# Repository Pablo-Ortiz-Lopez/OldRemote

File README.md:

## OldRemote

This repository consists of the reverse engineering of a garage remote design by spanish company JCM dated around 1995. It emits an ASK signal, which encodes the value of a physical trinary selector, using a 280MHz carrier wave.

### Contents
This repository contains the following files
* Schematic of the design (KiCad)
* Approximate PCB Layout of the design (KiCad)
* Datasheets of various components used

For more information, don't hesitate to check out my blog: [ortizma.com](https://ortizma.com), or contact me via [pabloortiz132@gmail.com](mailto:pabloortiz132@gmail.com)

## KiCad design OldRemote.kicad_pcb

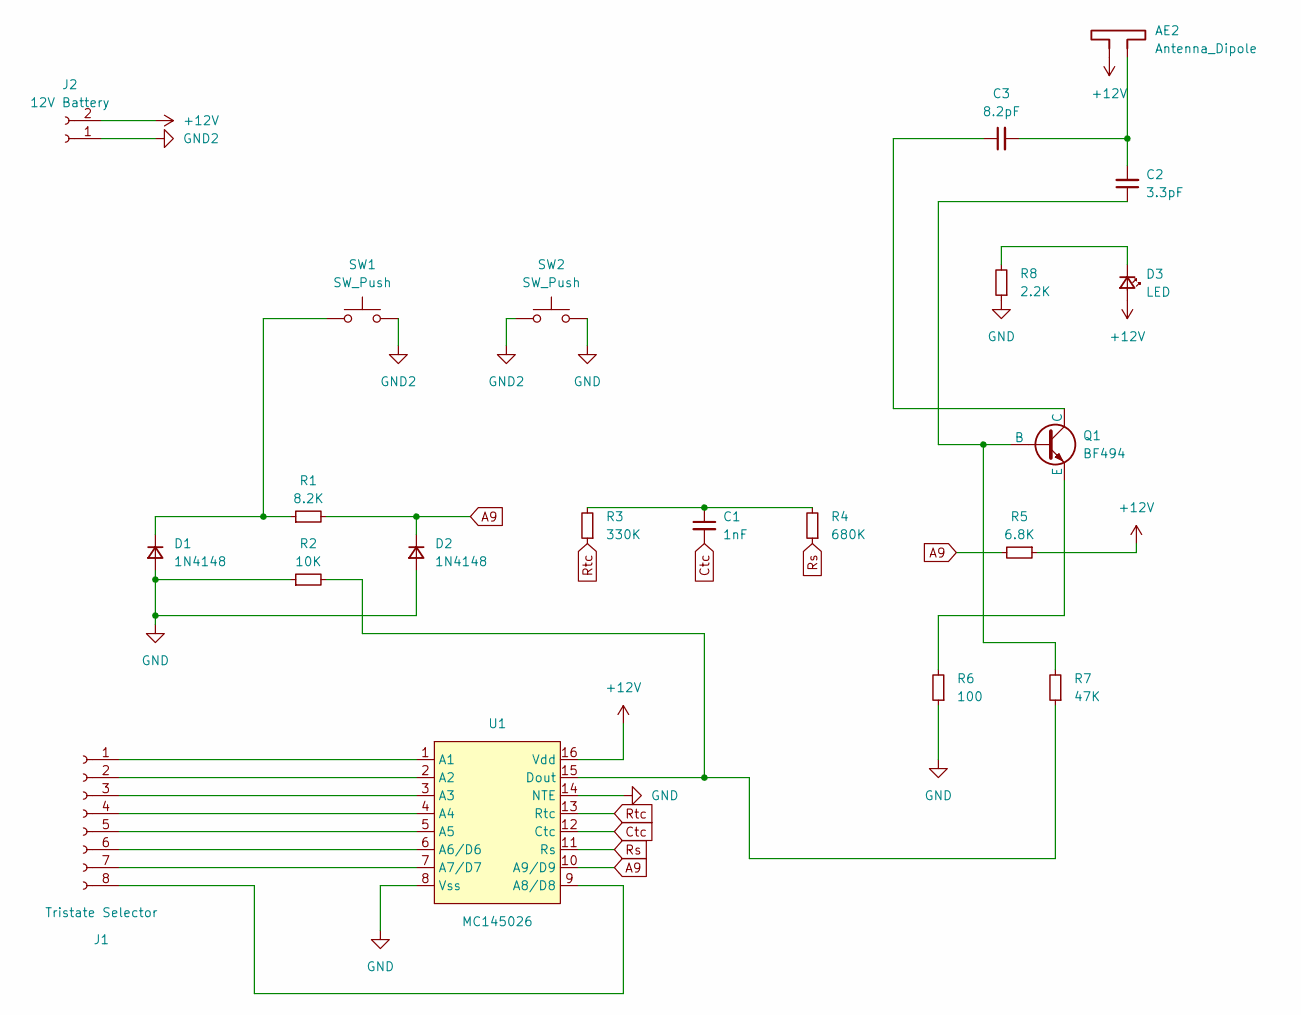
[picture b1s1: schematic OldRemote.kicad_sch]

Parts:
AE2: Antenna_Dipole; PinSocket_1x02_P2.54mm_Vertical
C1: 1nF; C_Rect_L4.0mm_W2.5mm_P2.50mm
C2: 3.3pF; C_Disc_D3.0mm_W1.6mm_P2.50mm
C3: 8.2pF; C_Disc_D3.0mm_W1.6mm_P2.50mm
D1, D2: 1N4148; D_DO-35_SOD27_P7.62mm_Horizontal
D3: LED; LED_D3.0mm_FlatTop
J1: Tristate Selector; PinSocket_1x08_P2.54mm_Horizontal
J2: 12V Battery; PinSocket_1x02_P2.54mm_Vertical
Q1: BF494; TO-92
R1: 8.2K; R_Axial_DIN0204_L3.6mm_D1.6mm_P5.08mm_Horizontal
R2: 10K; R_Axial_DIN0204_L3.6mm_D1.6mm_P5.08mm_Horizontal
R3: 330K; R_Axial_DIN0204_L3.6mm_D1.6mm_P5.08mm_Horizontal
R4: 680K; R_Axial_DIN0204_L3.6mm_D1.6mm_P5.08mm_Horizontal
R5: 6.8K; R_Axial_DIN0204_L3.6mm_D1.6mm_P5.08mm_Horizontal
R6: 100; R_Axial_DIN0204_L3.6mm_D1.6mm_P5.08mm_Horizontal
R7: 47K; R_Axial_DIN0204_L3.6mm_D1.6mm_P5.08mm_Horizontal
R8: 2.2K; R_Axial_DIN0204_L3.6mm_D1.6mm_P5.08mm_Horizontal
SW1, SW2: SW_Push; 4.5mm switch
U1: MC145026; DIP-16_W7.62mm

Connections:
+12V: AE2.1, D3.2 (A), J2.2, R5.1, U1.16 (Vdd)
A9: D2.1 (K), R1.2, R5.2, U1.10 (A9/D9)
Ctc: C1.2, U1.12 (Ctc)
GND: D1.2 (A), D2.2 (A), R2.1, R6.1, R8.1, SW2.2, U1.8 (Vss), U1.14 (NTE)
GND2: J2.1, SW1.2, SW2.1
unnamed: AE2.2, C2.2, C3.2
unnamed: C1.1, R3.2, R4.2
unnamed: D1.1 (K), R1.1, SW1.1
unnamed: D3.1 (K), R8.2
unnamed: J1.1, U1.1 (A1)
unnamed: J1.2, U1.2 (A2)
unnamed: J1.3, U1.3 (A3)
unnamed: J1.4, U1.4 (A4)
unnamed: J1.5, U1.5 (A5)
unnamed: J1.6, U1.6 (A6/D6)
unnamed: J1.7, U1.7 (A7/D7)
unnamed: J1.8, U1.9 (A8/D8)
unnamed: C2.1, Q1.2 (B), R7.2
unnamed: C3.1, Q1.1 (C)
unnamed: Q1.3 (E), R6.2
unnamed: R2.2, R7.1, U1.15 (Dout)
Rs: R4.1, U1.11 (Rs)
Rtc: R3.1, U1.13 (Rtc)

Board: 2 copper layers, 21 parts (0 on the bottom side), 23 nets, no tracks yet.

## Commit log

2023-09-27 Add trinary encoder datasheet
2023-09-29 Update schematic
